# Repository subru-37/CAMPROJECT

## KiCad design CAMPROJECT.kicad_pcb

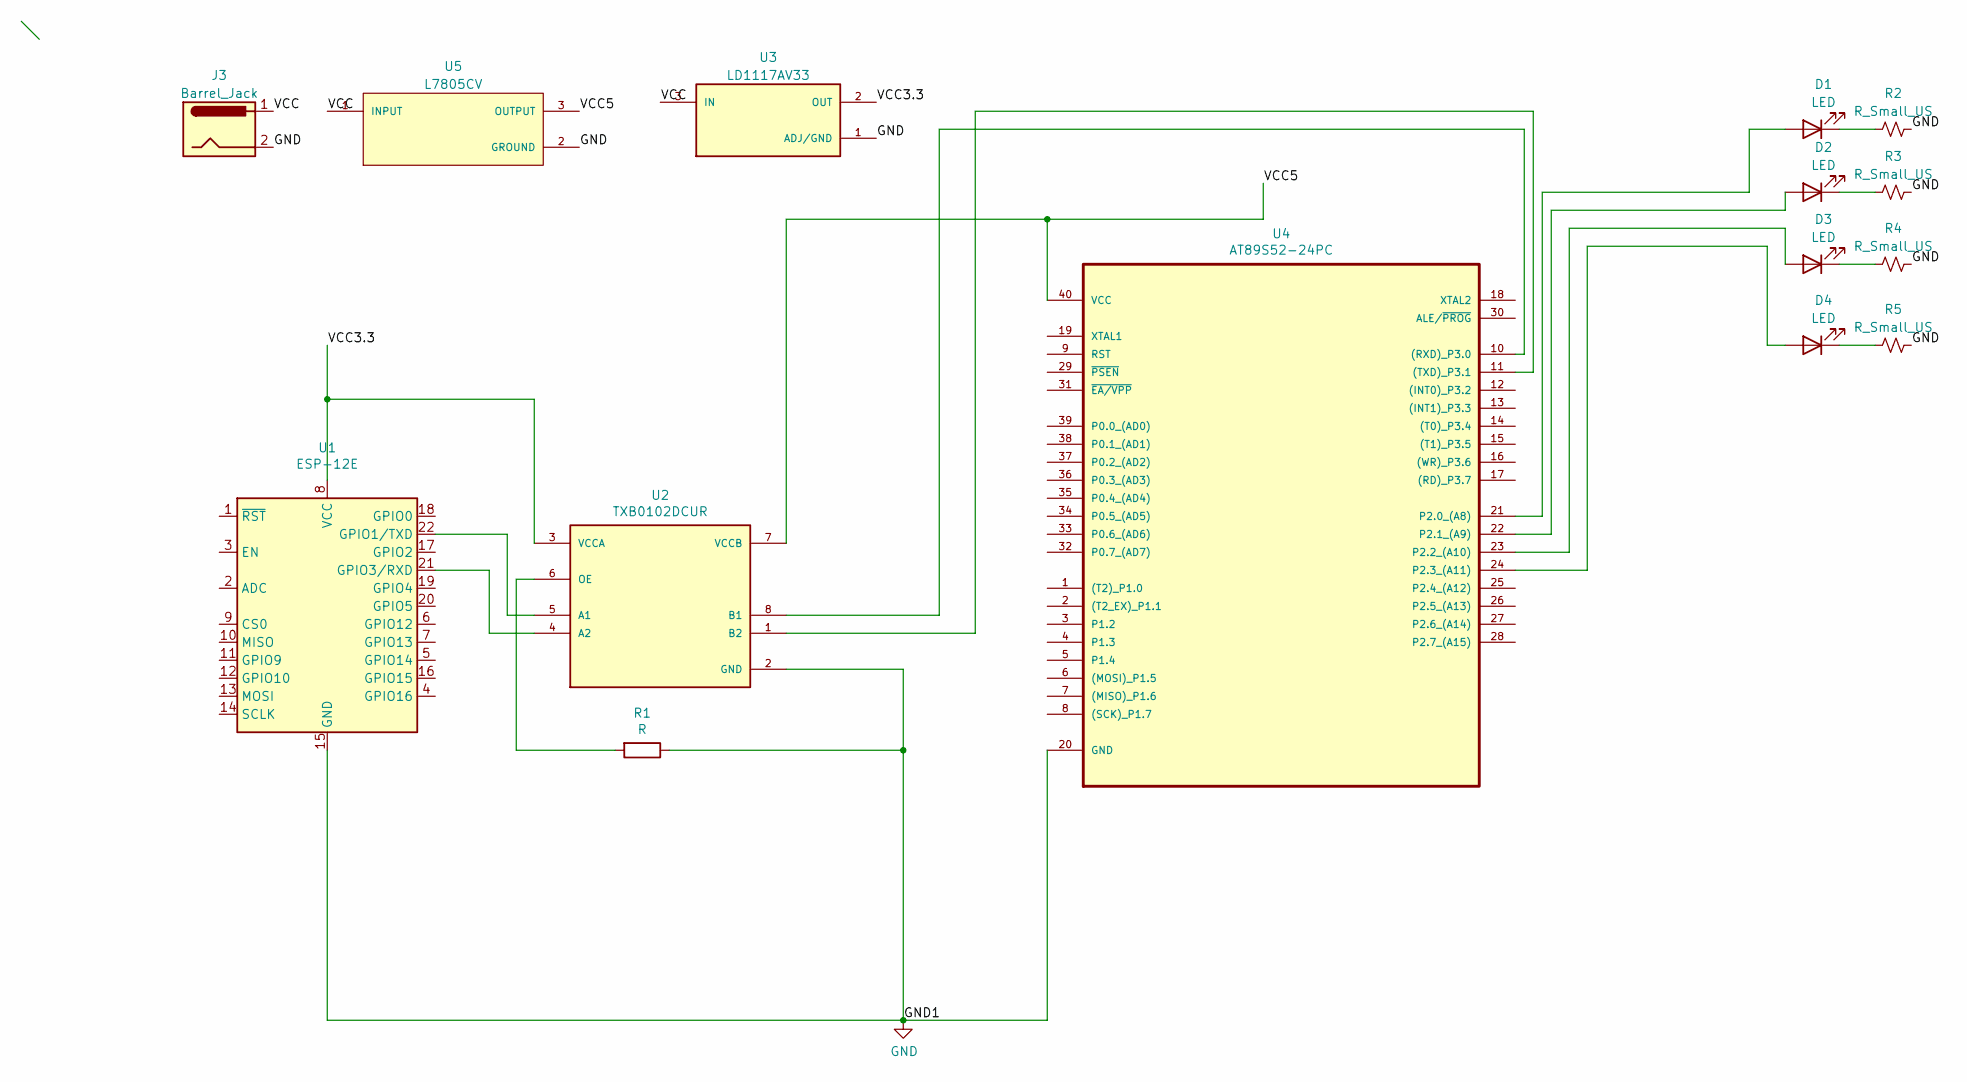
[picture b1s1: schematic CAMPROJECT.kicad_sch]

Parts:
D1, D2, D3, D4: LED; LED_D5.0mm_Clear
J3: Barrel_Jack; BarrelJack_GCT_DCJ200-10-A_Horizontal
R1: R; R_Axial_DIN0207_L6.3mm_D2.5mm_P10.16mm_Horizontal
R2, R3, R4, R5: R_Small_US; R_Axial_DIN0207_L6.3mm_D2.5mm_P10.16mm_Horizontal
U1: ESP-12E
U2: TXB0102DCUR; SOP50P310X90-8N; PARTREV D
U3: LD1117AV33; TO255P1020X450X1968-3; PARTREV 26
U4: AT89S52-24PC; DIP254P1524X482-40; MPN AT89S52-24PC
U5: L7805CV; TO255P1040X460X1968-3; PARTREV 36

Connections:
/VCC: J3.1, U3.3 (IN), U5.1 (INPUT)
/VCC3.3: U1.8 (VCC), U2.3 (VCCA), U3.2 (OUT)
/VCC5: U2.7 (VCCB), U4.40 (VCC), U5.3 (OUTPUT)
GND: J3.2, R1.1, R2.2, R3.2, R4.2, R5.2, U1.15 (GND), U2.2 (GND), U3.1 (ADJ/GND), U4.20 (GND), U5.2 (GROUND)
unnamed: D1.2 (A), U4.21 (P2.0_(A8))
unnamed: D1.1 (K), R2.1
unnamed: D2.2 (A), U4.22 (P2.1_(A9))
unnamed: D2.1 (K), R3.1
unnamed: D3.2 (A), U4.23 (P2.2_(A10))
unnamed: D3.1 (K), R4.1
unnamed: D4.2 (A), U4.24 (P2.3_(A11))
unnamed: D4.1 (K), R5.1
unnamed: U1.22 (GPIO1/TXD), U2.5 (A1)
unnamed: U1.21 (GPIO3/RXD), U2.4 (A2)
unnamed: U2.8 (B1), U4.10 ((RXD)_P3.0)
unnamed: U2.1 (B2), U4.11 ((TXD)_P3.1)
unnamed: R1.2, U2.6 (OE)

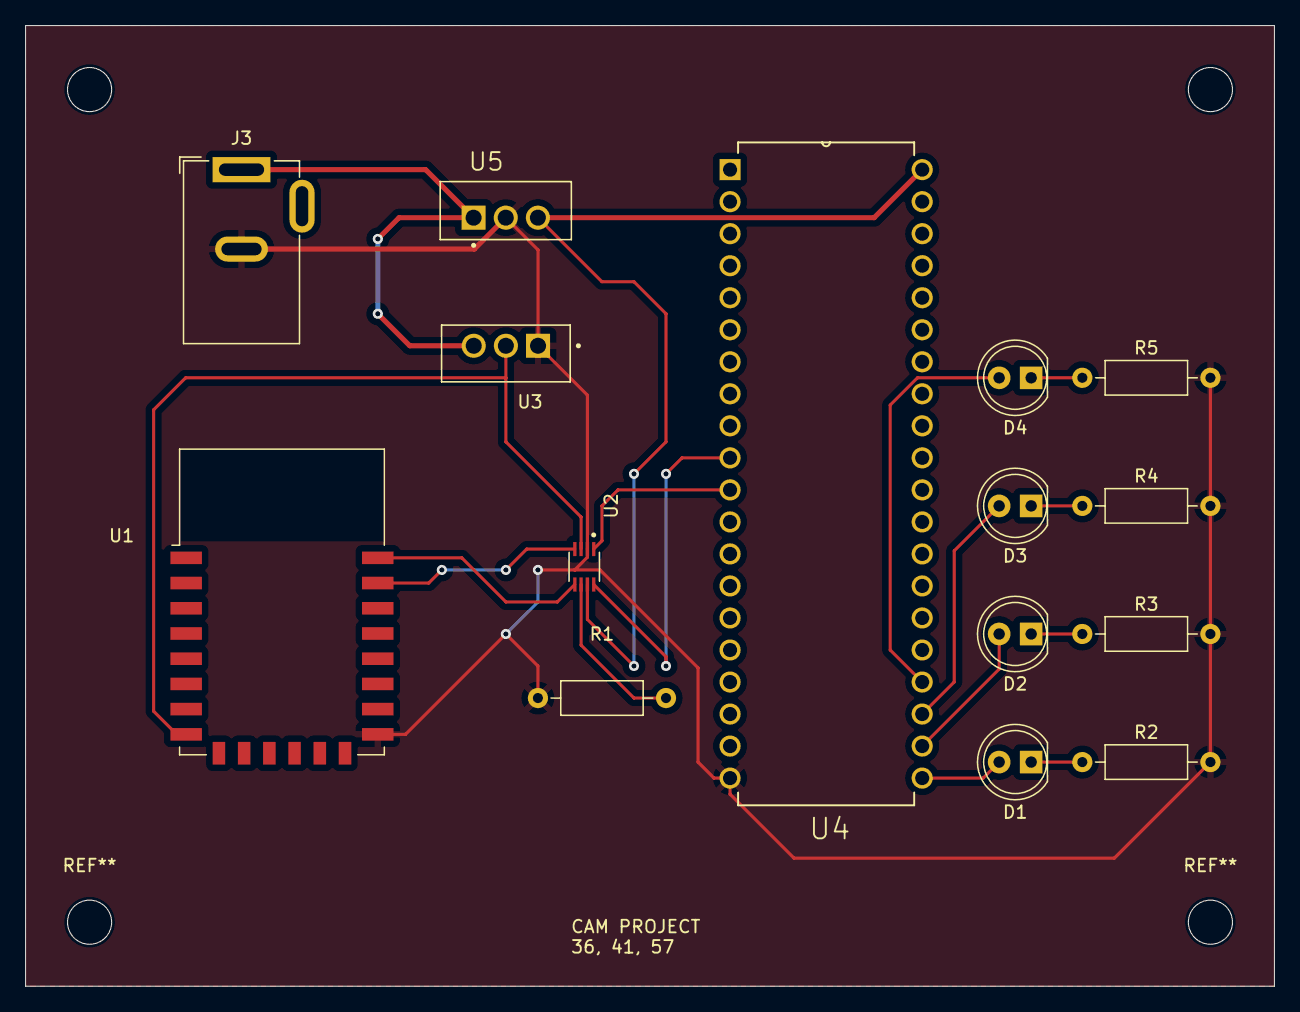
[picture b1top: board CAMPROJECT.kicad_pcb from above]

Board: 2 copper layers, 99.1 x 76.2 mm, 15 parts (0 on the bottom side), 17 nets.

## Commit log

2023-06-26 esp12e libraries
2023-06-26 esp12e code to receive and transmit command
2023-06-26 AT89S52 code to switch on/off pin outs
